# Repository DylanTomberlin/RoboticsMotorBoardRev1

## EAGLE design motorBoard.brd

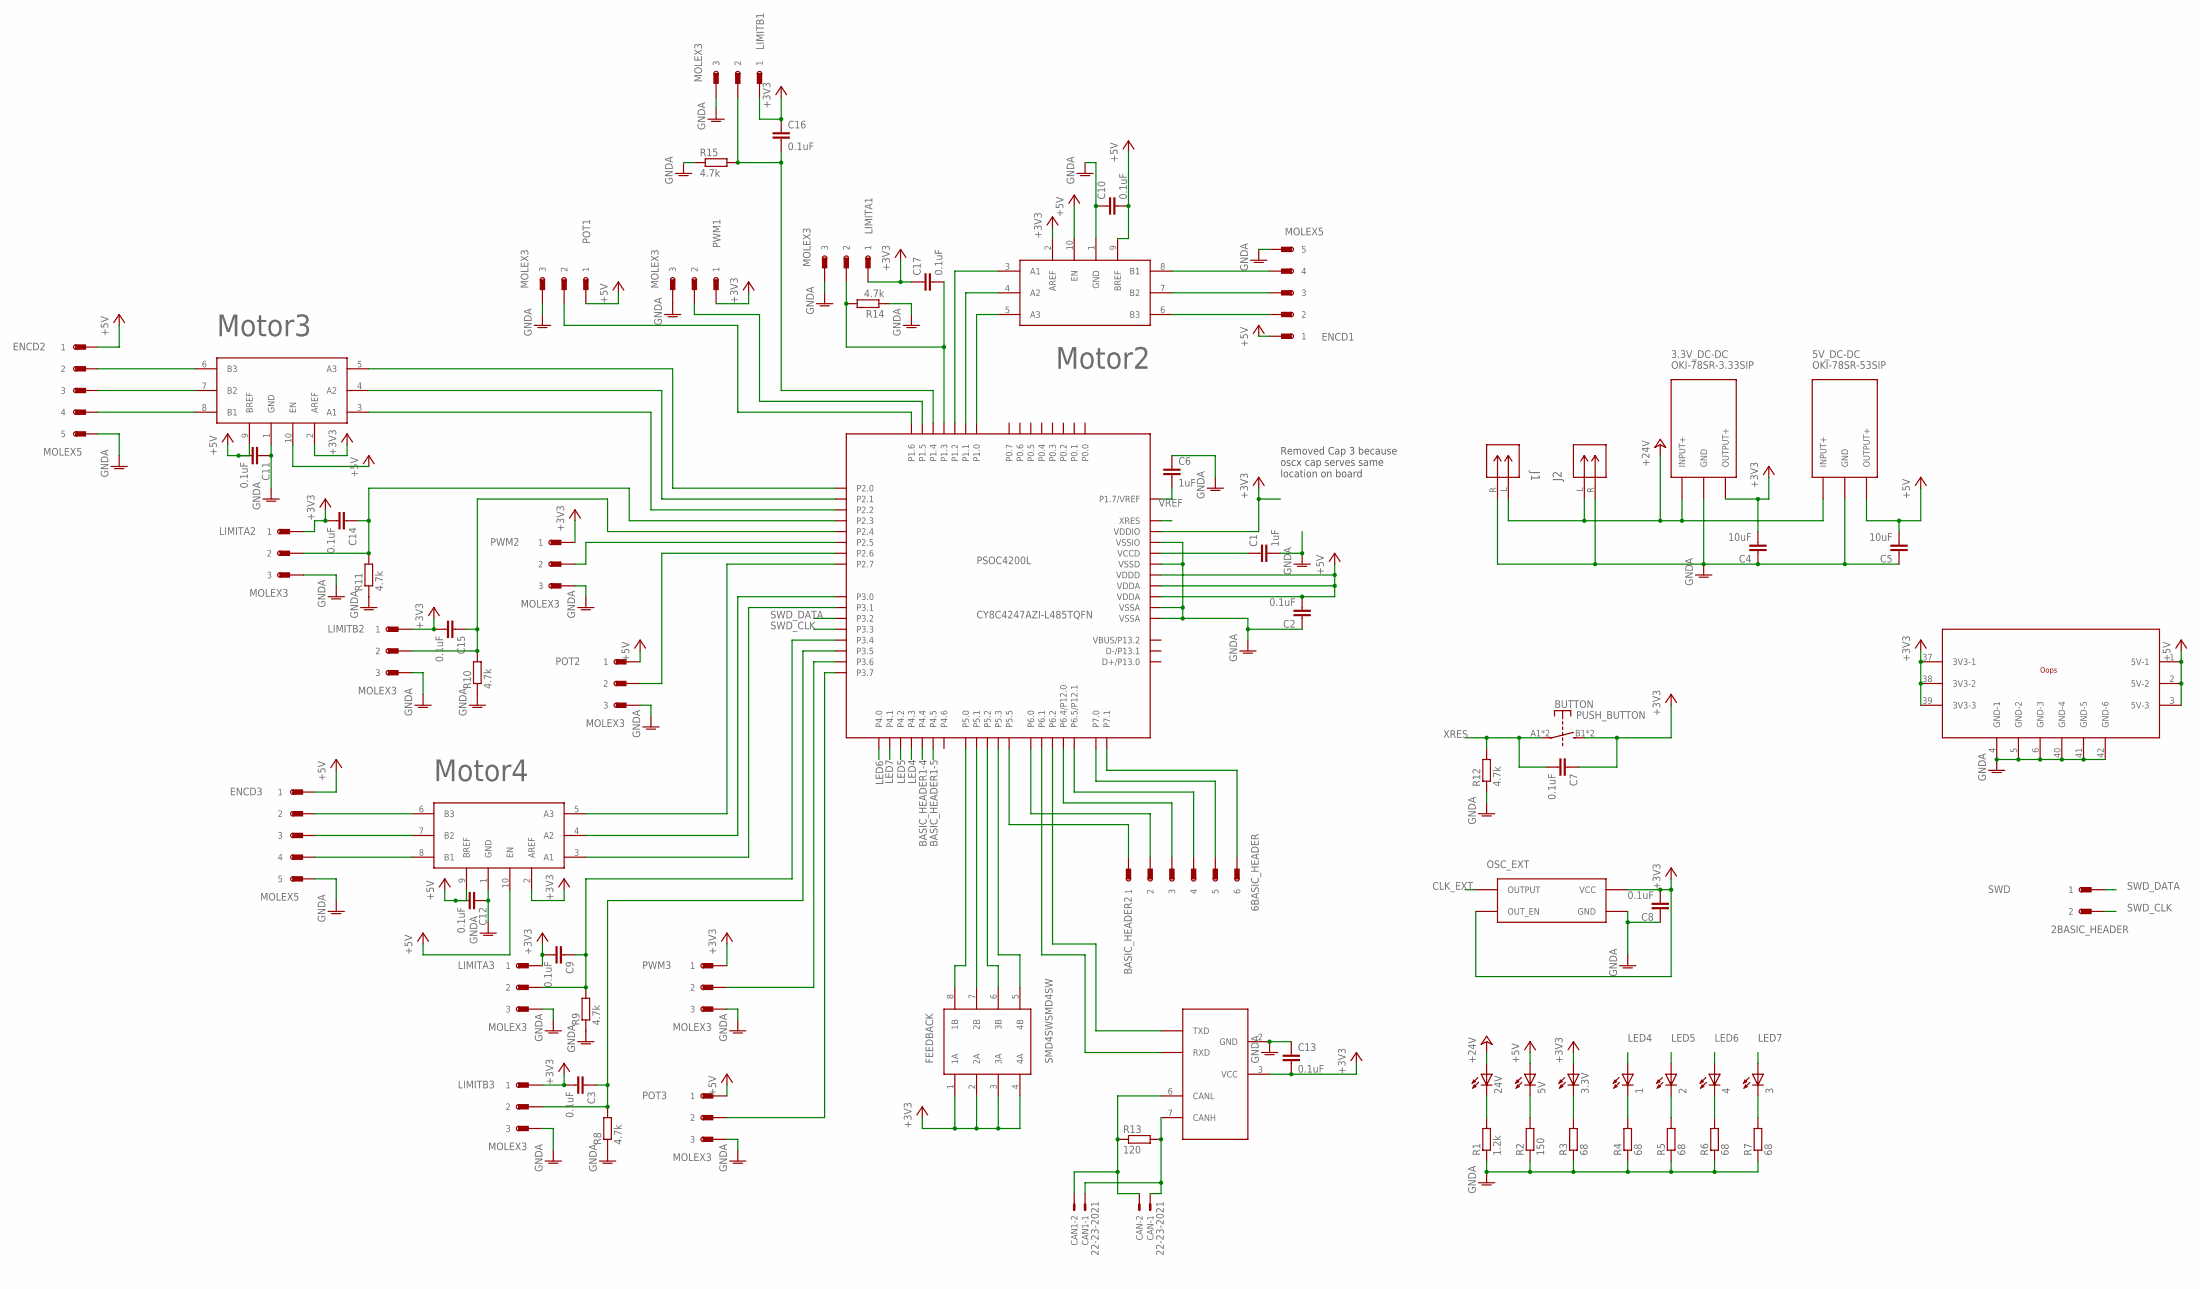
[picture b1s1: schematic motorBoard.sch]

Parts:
1, 2, 3, 3.3V, 4, 5V, 24V: LED_E; LED_1206
3.3V_DC-DC: OKI-78SR-3.33SIP; 3SIP
5V_DC-DC: OKI-78SR-53SIP; 3SIP
BASIC_HEADER2: 6BASIC_HEADER; 6SIP_HEADER
BUTTON: PUSH_BUTTON
C1, C6: 1uF; C1206
C2, C3, C7, C8, C9, C10, C11, C12, C13, C14, C15, C16, C17: 0.1uF; C1206
C4, C5: 10uF; C1206
CAN, CAN1: 22-23-2021
ENCD1, ENCD2, ENCD3: MOLEX5; MOLEX22-23-2051
FEEDBACK: SMD4SWSMD4SW; GULL8
J1, J2: TE-TERM-BLOCK
LIMITA1, LIMITA2, LIMITA3: MOLEX3; MOLEX22-23-2031
LIMITB1, LIMITB2, LIMITB3: MOLEX3; MOLEX22-23-2031
OSC_EXT: ESPSON_SG-646PCE_CRYSTAL_OSCILLATOREPSON_SG-646PC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; 4SOJ-5.08MM
POT1, POT2, POT3: MOLEX3; MOLEX22-23-2031
PROTOTYPINGSPACE: OOPS_SPACESMALL; OOPS_SPACE_SMALL
PSOC4200L: CY8C4247AZI-L485TQFN; TQPF64-10MM
PWM1, PWM2, PWM3: MOLEX3; MOLEX22-23-2031
R1: 1.2k; R1206
R2: 150; R1206
R3, R4, R5, R6, R7: 68; R1206
R8, R9, R10, R11, R12, R14, R15: 4.7k; R1206
R13: 120; R1206
SHIFT2, SHIFT3, SHIFT4: LEVEL-SHIFTER_NVT2003DPNVT_2003DP_LEVEL_SHIFTER; TSSOP10
SWD: 2BASIC_HEADER; 2SIP_HEADER
TCAN: TCAN332TCAN332; 8SOIC3.9

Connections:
+3V3: 3.3V.A, 3.3V_DC-DC.3 (OUTPUT+), BUTTON.B1 (S), BUTTON.B2 (S), C3.2, C4.2, C7.1, C8.2, C9.2, C13.2, C14.2, C15.2, C16.1, C17.1, FEEDBACK.1 (1A), FEEDBACK.2 (2A), FEEDBACK.3 (3A), FEEDBACK.4 (4A), LIMITA1.1, LIMITA2.1, LIMITA3.1, LIMITB1.1, LIMITB2.1, LIMITB3.1, OSC_EXT.1 (OUT_EN), OSC_EXT.4 (VCC), PROTOTYPINGSPACE.37 (3V3-1), PROTOTYPINGSPACE.38 (3V3-2), PROTOTYPINGSPACE.39 (3V3-3), PSOC4200L.26 (VDDIO), PWM1.1, PWM2.1, PWM3.1, SHIFT2.2 (AREF), SHIFT3.2 (AREF), SHIFT4.2 (AREF), TCAN.3 (VCC)
+5V: 5V.A, 5V_DC-DC.3 (OUTPUT+), C2.2, C5.2, C10.2, C11.2, C12.2, ENCD1.1, ENCD2.1, ENCD3.1, POT1.1, POT2.1, POT3.1, PROTOTYPINGSPACE.1 (5V-1), PROTOTYPINGSPACE.2 (5V-2), PROTOTYPINGSPACE.3 (5V-3), PSOC4200L.11 (VDDA), PSOC4200L.50 (VDDD), PSOC4200L.56 (VDDA), SHIFT2.9 (BREF), SHIFT2.10 (EN), SHIFT3.9 (BREF), SHIFT3.10 (EN), SHIFT4.9 (BREF), SHIFT4.10 (EN)
+24V: 3.3V_DC-DC.1 (INPUT+), 5V_DC-DC.1 (INPUT+), 24V.A, J1.L (1), J2.L (1)
BASIC_HEADER1-4: PSOC4200L.31 (P4.4)
BASIC_HEADER1-5: PSOC4200L.32 (P4.5)
BASIC_HEADER2-1: BASIC_HEADER2.1, PSOC4200L.55 (P5.5)
BASIC_HEADER2-2: BASIC_HEADER2.2, PSOC4200L.12 (P6.0)
BASIC_HEADER2-3: BASIC_HEADER2.3, PSOC4200L.15 (P6.4/P12.0)
BASIC_HEADER2-4: BASIC_HEADER2.4, PSOC4200L.16 (P6.5/P12.1)
BASIC_HEADER2-5: BASIC_HEADER2.5, PSOC4200L.37 (P7.0)
BASIC_HEADER2-6: BASIC_HEADER2.6, PSOC4200L.38 (P7.1)
CANH: CAN.1, CAN1.1, R13.2, TCAN.7 (CANH)
CANL: CAN.2, CAN1.2, R13.1, TCAN.6 (CANL)
CANRX: PSOC4200L.13 (P6.1), TCAN.4 (RXD)
CANTX: PSOC4200L.14 (P6.2), TCAN.1 (TXD)
CLK_EXT: OSC_EXT.3 (OUTPUT)
GNDA: 3.3V_DC-DC.2 (GND), 5V_DC-DC.2 (GND), C1.2, C2.1, C4.1, C5.1, C6.1, C8.1, C10.1, C11.1, C12.1, C13.1, ENCD1.5, ENCD2.5, ENCD3.5, J1.R (2), J2.R (2), LIMITA1.3, LIMITA2.3, LIMITA3.3, LIMITB1.3, LIMITB2.3, LIMITB3.3, OSC_EXT.2 (GND), POT1.3, POT2.3, POT3.3, PROTOTYPINGSPACE.4 (GND-1), PROTOTYPINGSPACE.5 (GND-2), PROTOTYPINGSPACE.6 (GND-3), PROTOTYPINGSPACE.40 (GND-4), PROTOTYPINGSPACE.41 (GND-5), PROTOTYPINGSPACE.42 (GND-6), PSOC4200L.10 (VSSA), PSOC4200L.17 (VSSIO), PSOC4200L.49 (VSSD), PSOC4200L.57 (VSSA), PWM1.3, PWM2.3, PWM3.3, R1.1, R2.1, R3.1, R4.1, R5.1, R6.1, R7.1, R8.1, R9.1, R10.1, R11.1, R12.1, R14.1, R15.1, SHIFT2.1 (GND), SHIFT3.1 (GND), SHIFT4.1 (GND), TCAN.2 (GND)
LED4: 1.A, PSOC4200L.30 (P4.3)
LED5: 2.A, PSOC4200L.29 (P4.2)
LED6: 4.A, PSOC4200L.27 (P4.0)
LED7: 3.A, PSOC4200L.28 (P4.1)
MOTOR2A1: PSOC4200L.60 (P1.2), SHIFT2.3 (A1)
MOTOR2A2: PSOC4200L.59 (P1.1), SHIFT2.4 (A2)
MOTOR2A3: PSOC4200L.58 (P1.0), SHIFT2.5 (A3)
MOTOR2B1: ENCD1.4, SHIFT2.8 (B1)
MOTOR2B2: ENCD1.3, SHIFT2.7 (B2)
MOTOR2B3: ENCD1.2, SHIFT2.6 (B3)
MOTOR2LIMA: C17.2, LIMITA1.2, PSOC4200L.61 (P1.3), R14.2
MOTOR2LIMB: C16.2, LIMITB1.2, PSOC4200L.62 (P1.4), R15.2
MOTOR2POT: POT1.2, PSOC4200L.64 (P1.6)
MOTOR2PWM: PSOC4200L.63 (P1.5), PWM1.2
MOTOR3A1: PSOC4200L.4 (P2.2), SHIFT3.3 (A1)
MOTOR3A2: PSOC4200L.3 (P2.1), SHIFT3.4 (A2)
MOTOR3A3: PSOC4200L.2 (P2.0), SHIFT3.5 (A3)
MOTOR3B1: ENCD2.4, SHIFT3.8 (B1)
MOTOR3B2: ENCD2.3, SHIFT3.7 (B2)
MOTOR3B3: ENCD2.2, SHIFT3.6 (B3)
MOTOR3LIMA: C14.1, LIMITA2.2, PSOC4200L.5 (P2.3), R11.2
MOTOR3LIMB: C15.1, LIMITB2.2, PSOC4200L.6 (P2.4), R10.2
MOTOR3POT: POT2.2, PSOC4200L.8 (P2.6)
MOTOR3PWM: PSOC4200L.7 (P2.5), PWM2.2
MOTOR4A1: PSOC4200L.19 (P3.1), SHIFT4.3 (A1)
MOTOR4A2: PSOC4200L.18 (P3.0), SHIFT4.4 (A2)
MOTOR4A3: PSOC4200L.9 (P2.7), SHIFT4.5 (A3)
MOTOR4B1: ENCD3.4, SHIFT4.8 (B1)
MOTOR4B2: ENCD3.3, SHIFT4.7 (B2)
MOTOR4B3: ENCD3.2, SHIFT4.6 (B3)
MOTOR4LIMA: C9.1, LIMITA3.2, PSOC4200L.22 (P3.4), R9.2
MOTOR4LIMB: C3.1, LIMITB3.2, PSOC4200L.23 (P3.5), R8.2
MOTOR4POT4: POT3.2, PSOC4200L.25 (P3.7)
MOTOR4PWM: PSOC4200L.24 (P3.6), PWM3.2
unnamed: 24V.C, R1.2
unnamed: 5V.C, R2.2
unnamed: 3.3V.C, R3.2
unnamed: 1.C, R4.2
unnamed: 2.C, R5.2
unnamed: 4.C, R6.2
unnamed: 3.C, R7.2
SEL_SW1: FEEDBACK.8 (1B), PSOC4200L.51 (P5.0)
SEL_SW2: FEEDBACK.7 (2B), PSOC4200L.52 (P5.1)
SEL_SW3: FEEDBACK.6 (3B), PSOC4200L.53 (P5.2)
SEL_SW4: FEEDBACK.5 (4B), PSOC4200L.54 (P5.3)
SWD_CLK: PSOC4200L.21 (P3.3), SWD.2
SWD_DATA: PSOC4200L.20 (P3.2), SWD.1
VCCD: C1.1, PSOC4200L.48 (VCCD)
VREF: C6.2, PSOC4200L.1 (P1.7/VREF)
XRES: BUTTON.A1, BUTTON.A2, C7.2, PSOC4200L.47 (XRES), R12.2

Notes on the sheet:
Motor2
Motor3
Motor4
Removed Cap 3 because oscx cap serves same location on board

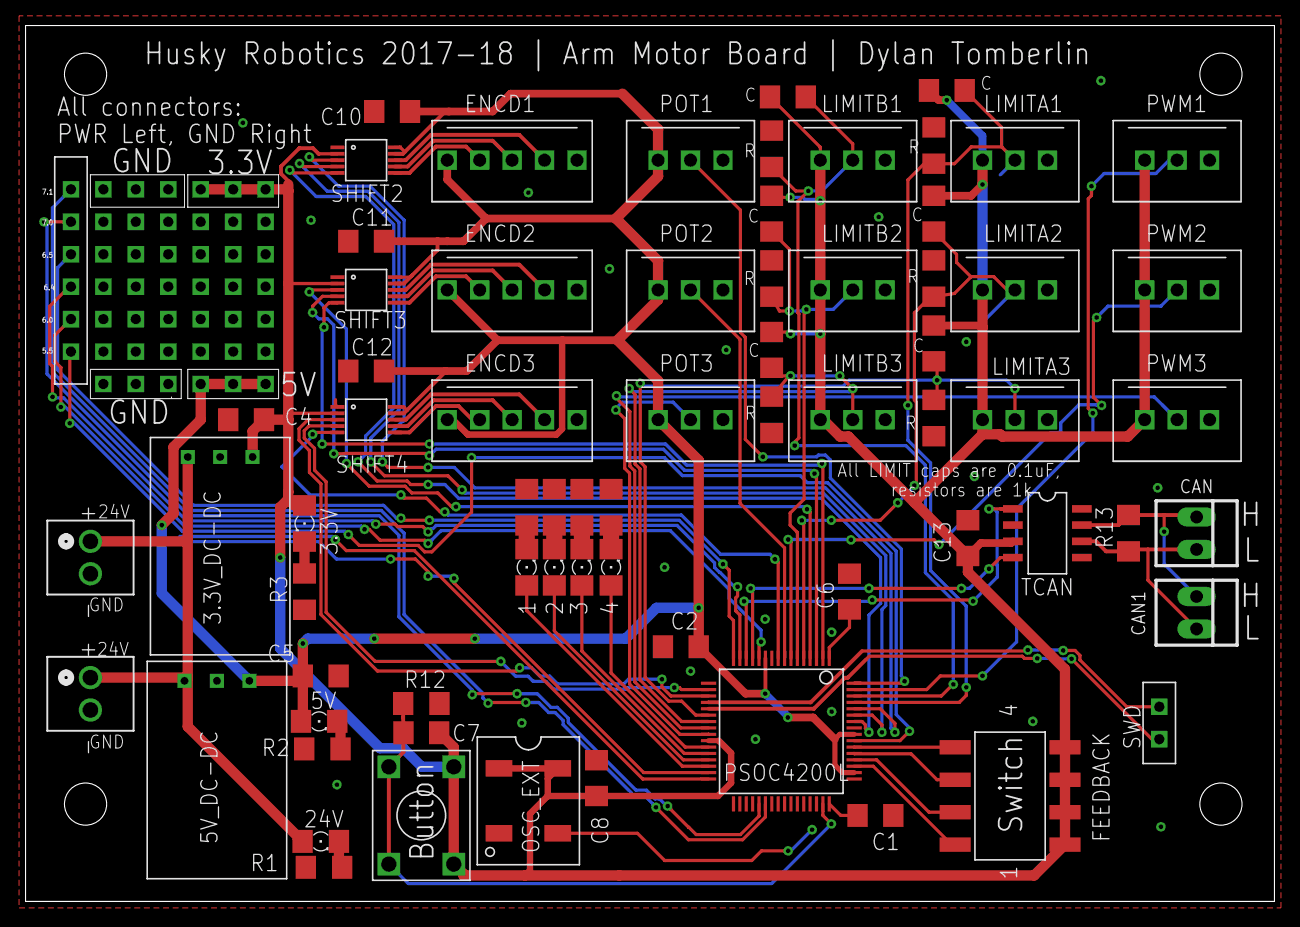
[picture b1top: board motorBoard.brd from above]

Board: 2 copper layers, 97.8 x 68.6 mm, 71 parts (0 on the bottom side), 64 nets.

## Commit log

2018-01-11 Added level shifter
    TSSOP10 package, NVT2003 (level shifter) symbol, LEVEL-SHIFTER_NVT2003DP device (links this package and symbol).
2018-01-11 Minor Tweaks
    Added a couple of ground and voltage references.
2018-01-11 Finishing touches on the schematic
    Added indicator LEDs, labeled all nets, spare gpio headers, cleaned up schematic, other misc. Quickie layout and auto router just for funsies.
2018-01-11 Change CLK_EXT pin
    Had to move LED5, Motor1LimitSwitch as well.
2018-01-13 Added decoupling caps, schematic tweaks, layout, mid routing
    Running out of space around PSoC, so I need to rework my component layout.
2018-01-13 3x5in board, more room for better routing
    Worked on routing
2018-01-13 save before auto route test
2018-01-13 Needs final touches
    Used the auto router for some of the tiny routing around the PSoC which I was struggling with. TIme for some food and sleep now. Could someone else please finish up the last little trouble shooting?
2018-01-16 Finished Board
    Ready for Review
2018-01-16 Revert "Finished Board"
    This reverts commit 761fd842cb1d32e6d861dcd06b5bacfd84886b14.
2018-01-16 Ground plane tweaks
2018-01-17 Meeting updates
2018-01-17 Fixed Git Issues
    If this push works, this should be the end of the git-astrophe.
2018-01-17 Mostly done with the small board
    Removed 1 motor channel, all 3V3 encoders, level shifter enable switches, 1 gpio header. Moved around a ton of components.
2018-01-19 "Done" except for silk screen and DFM check
    Added 24V terminal blocks, second CAN header, limit switch debounces.
2018-01-19 Finished Silk Screening
    Ready for DFM test!
2018-01-19 Created Gerber Files Round1
2018-01-19 Made changes for Bay Area Circuits DFM
    Re-Zipped
2018-01-23 Aesthetic Changes
    Changed Layer Fill, Moved text around, Generated Pictures
2018-01-28 Changed Resistor Values
    Now match that of order
2018-01-31 Cleaned Up Schematic
